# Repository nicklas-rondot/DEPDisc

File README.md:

# DEPDisc
The DEPDisc platform is the first implementation of dielectrophoresis where both the equipment and the consumables are truly inexpensive. It utilizes CD microfluidics to allow the integration of DEP with other microfluidic operations. 
All aspects of the DEPDisc platform are open-source, including the fabrication technique for the discs (with example designs) and the device.
While the paper presents the underlying theory and the results of the DEPDisc platform, this repository is intended to provide the necessary information to reproduce the platform.

This version is from the 06th of October 2024. A more current version might be available at https://github.com/nicklas-rn/DEPDisc.

## Table of Contents
- [Discs](#Discs)
- [Device](#Device)
- [How to Run](<#How to Run>)
- [Additional Figures](<#Additional Figures>)

## Discs
In the folder [Discs](/Discs), the design files for the discs can be found. The PCB files can be used in Eagle or Fusion360 Electronics. [Example Disc PCBs](/Discs/Example%20Disc%20PCBs) are provided as inspiration. The separate [coil PCB](/Discs/Coil%20PCB/) used as transmitter is included as well. For new designs, the [coil PCB library](/Discs/Coil%20PCB%20Library/) can be used.

## Device
The [Device CAD and PCB folder](/Device/) contains all the necessary files to reproduce the DEPDisc device. The device is composed of a PCB, off-the-shelf components, and a set of 3D printed parts. 

### PCB
To order the PCB at [JLCPCB](https://jlcpcb.com), the [Manufacturing folder](/Device/PCB/Manufacturing/) with a [ZIP file](/Device/PCB/Manufacturing/DEPDisc%20Base%20rev1%20v8_2024-09-17.zip) of the Gerber files is included. For assembly by JLCPCB, the [BOM file](/Device/PCB/Manufacturing/DEPDisc%20Base%20rev1%20v8_2024-09-17.zip) and [Pick and Place file](/Device/PCB/Manufacturing/DEPDisc%20Base%20rev1%20v8_2024-09-17.zip) are also provided. 
The ordering process is the follwing:
1. Go to [JLCPCB](https://jlcpcb.com)
2. Click on **Add gerber file** and upload the ZIP file
3. Select the desired options and **Enable PCB Assembly** (choose 2 as PCBA quantity instead of 5). Select **Bottom Side Assembly**.
4. After clicking **Next**, upload the **BOM file** and **CPL (Pick and Place) file**, then continue
5. When reviewing the parts, ensure that only C13 and JP3 show 'No part selected' and that the rest of the parts are correctly assigned. Then click **Next** and then **Do not Place** upon the prompt showing that the project has unselected parts.
6. Review the part placement and click **Next**, then click **Save to Cart**
7. Review the order and click **Secure Checkout**

The [design files](/Device/PCB/Design%20Files) of the PCB for Eagle or Fusion360 Electronics are included in case this project is used as inspiration or if modifications are desired.

### Housing
The [parts for printing](/Device/3D%20Printed%20Parts) are provided as STL files. In the slicer, we recommend enabling tree-supports. 
A [STEP file](/Device/DEPDisc%20Device%20rev1.step) of the assembly is included. 

### Assembly
To assemble the device, use the following procedure:
1. Place M3 nuts in all the provided slots in the 3D printed parts.
2. Solder the pin-headers to the PCB: 
3. Solder two jumper wires to the motor: 
4. Plug the ESP32 NodeMCU Dev board into the pin-headers: 
5. Screw the touch display to the display mount: 
6. Plug in 14 female-to-female jumper wires to the display. We recommend placing tape around the ends to keep the wires together when they are removed: 
7. Plug the other side of the jumper wires into the PCB: 
8. Slide the PCB into the left side of the inner shell of the housing and move the motor through the hole: 
9. Screw the motor in place with two M1.2 screws: 
10. Slide the display in to the right side of the inner shell of the housing: 
11. Screw the display in place from the bottom with four M3 screws: 
12. Connect the two inner shell sides with three M3 screws:  
13. Place the right side of the outer shell on top of the inner shell by carefully bending it slightly: 
14. Push the aluminium rod through the left side of the outer shell and the hatch: 
15. Push the left side of the outer shell on top of the inner shell by moving it in from the left and carefully bending it slightly:  
16. Screw six M3 screws into the outer shell: 

### Programming
To program the device, use the [Arduino file](/Device/Software/DEPDisc_base.ino) provided in the [Software folder](/Device/Software). Use to following procedure:
1. Download the Arduino IDE
2. Install the ESP32 boards under the boards manager (Second tab from the top, type 'esp32' in the search bar, and click install)
3. Click on Tools -> Board -> esp32 -> ESP32 Dev Module
4. Select the correct port under Tools -> Port
5. Click on the upload button (right arrow) to upload the code to the ESP32

## How to Run
### Experimental mode
Connect the device with a USB cable to a laptop. Use the Serial Monitor of the Arduino IDE and select a Baud Rate of 115200. 
To set a specific frequency, type: `freq [frequency in Hz]`
To set a specific speed, type: spin `[PWM value between -255 and 255]`

### Run from SD card
Write a text file with the name **run.txt** to the SD card with the same commands as above. Between the commands use a newline. Use the command `delay [delay in seconds]` to set delays. Insert the SD card into the device and select 'Run from SD card'. The device will read the file and execute the commands.

## Additional Figures
- [A video showing the attraction of yeast cells to the edges of two electrodes](/Figures/dep_edge.mov).

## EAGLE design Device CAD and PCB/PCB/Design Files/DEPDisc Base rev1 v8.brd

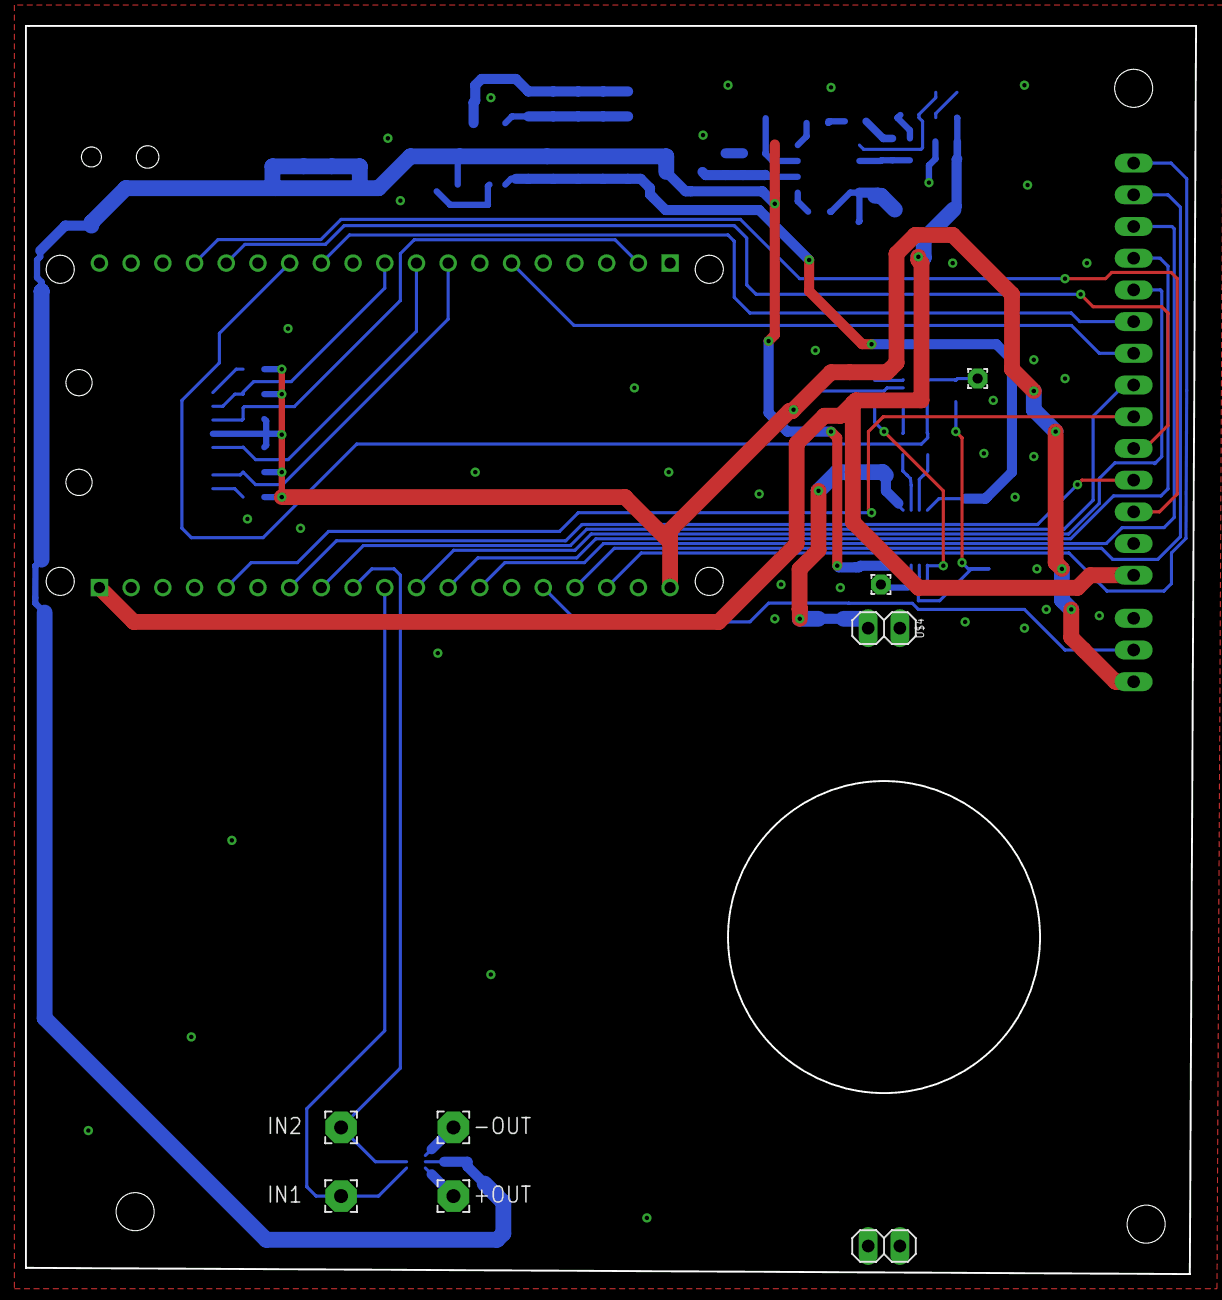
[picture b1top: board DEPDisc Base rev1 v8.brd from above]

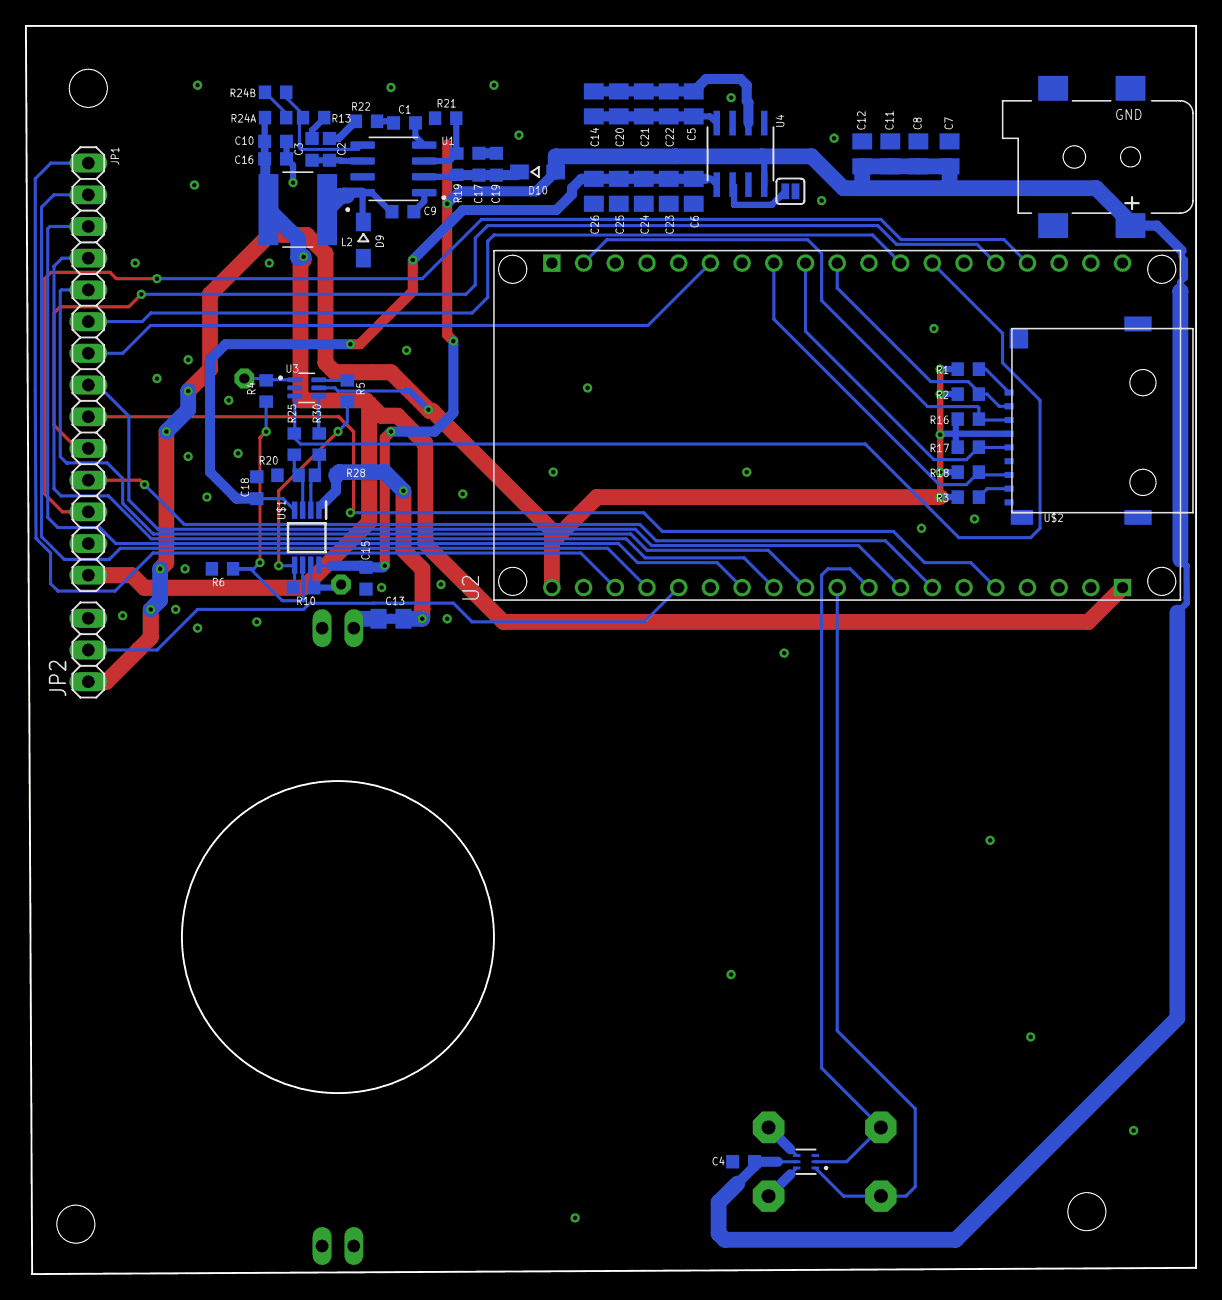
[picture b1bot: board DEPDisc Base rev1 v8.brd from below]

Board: 2 copper layers, 93.8 x 100.0 mm, 68 parts (60 on the bottom side), 50 nets.

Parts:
+OUT: 2,54/1,1
-OUT: 2,54/1,1
AMPIN2: 1,6/0,8
AMPOUT2: 1,6/0,8
C1, C17: 10nF; C0603K
C2: 1nF; C0603K
C3: 47pF; C0603K
C4, C9, C15, C18: 100nF; C0603K
C5, C6, C7, C8, C11, C12, C14, C20, C21, C22, C23, C24, C25, C26: 22uF; C0805K
C10, C16: 47uF; C0603K
C13: DNP; C0805K
C19: 10uF; C0603K
CN1: DC-005-2.5A-2.0-SMT; DCJACK_2MM_SMT
D9, D10: 1N5819WS; SOD323-W
IN1, IN2: 2,54/1,1
JP1: 1X14
JP2: 1X03
JP3: JUMPER-SMT_2_NC_PASTE_SILK; SMT-JUMPER_2_NC_PASTE_SILK
L2: 1255AY-6R8M=P3; IND_1255AY-6R8M=P3
R1, R2, R3, R16, R17, R18: 47k; R0603
R4, R5, R24B: 510; R0603
R6, R10: 1k; R0603
R13, R20, R28: 2k; R0603
R19: 332k; R0603
R21: 68.1k; R0603
R22: 29.4k; R0603
R24A: 10k; R0603
R25, R30: 750; R0603
U1: TPS54331DR; SOIC127P599X175-8N
U2: ESP32_NODEMCU; MODULE_ESP32_NODEMCU
U3: SN74LVC2G04DCKR; SOT65P210X110-6N
U4: ICL7662EBA-T; 21-0041B_8
U5: DRV8220DRLRSOT5X3-6_DRL_TEX-L; SOT5X3-6_DRL_TEX-L
U$1: OPA2810IDGKR; SOP65P490X110-8N
U$2: MICROSD-PUSH-OUT
U$3, U$4: PINHD-1X02_1X02M; 1X02

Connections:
+3V3: JP2.1, R1.1, R2.1, R3.1, R16.1, R17.1, R18.1, U2.J5_19, U3.5, U$2.4
+5V: C10.1, C16.1, JP1.14, L2.2, R24A.2, U2.J5_1
+12V: C4.1, C7.2, C8.2, C11.2, C12.2, C15.1, CN1.PWR1, D10.A, U4.8, U5.5, U$1.8
+IN1: R25.2, U2.J4_13, U3.3
+IN1R: R20.2, R25.1, U$1.3
+IN2: AMPIN2.1, R4.2, U3.1
+IN2R: R4.1, R6.2, U$1.6
-12V: C6.2, C18.1, C23.2, C24.2, C25.2, C26.2, U4.5, U$1.4
-IN1: R30.2, U3.4
-IN1R: R28.1, R30.1, U$1.2
-IN2: R5.2, U3.6
-IN2R: R5.1, R10.1, U$1.5
AMP1: C13.1, C13.2, R28.2, U$1.1, U$4.1
AMP2: AMPOUT2.1, R10.2, U$1.7
DAT2: R1.2, U$2.1
GND: C1.2, C3.2, C4.2, C6.1, C7.1, C8.1, C10.2, C11.1, C12.1, C15.2, C16.2, C17.2, C18.2, C19.2, C23.1, C24.1, C25.1, C26.1, CN1.GND, CN1.GNDBREAK, D9.A, JP1.13, JP2.3, JP3.2, R6.1, R13.1, R20.1, R21.1, R22.1, U1.7, U2.J4_1, U2.J4_7, U2.J5_6, U3.2, U4.3, U5.3, U$2.6, U$2.G1, U$2.G2, U$2.G3, U$2.G4, U$4.2
IO2: JP1.10, U2.J4_15
IO5: R2.2, U2.J4_10, U$2.2
IO12: JP1.11, U2.J5_7
IO13: JP1.9, U2.J5_5
IO14: JP1.8, U2.J5_8
IO15: JP1.12, U2.J4_16
IO16: JP1.6, U2.J4_12
IO18: R17.2, U2.J4_9, U$2.5
IO19: R18.2, U2.J4_8, U$2.7
IO21: JP1.7, U2.J4_6
IO23: R16.2, U2.J4_2, U$2.3
IO25: JP1.5, U2.J5_11
IO26: IN1.1, U2.J5_10, U5.1
IO27: IN2.1, U2.J5_9, U5.2
IO32: JP1.3, U2.J5_13
IO33: JP1.4, U2.J5_12
IO34: JP2.2, U2.J5_15
IO36: JP1.1, U2.J5_17
IO39: JP1.2, U2.J5_16
unnamed: C5.2, C14.2, C20.2, C21.2, C22.2, U4.2
unnamed: C5.1, C14.1, C20.1, C21.1, C22.1, U4.4
unnamed: +OUT.1, U5.6
unnamed: -OUT.1, U5.4
unnamed: JP3.1, U4.6
unnamed: R19.2, R21.2, U1.3
unnamed: C1.1, U1.4
unnamed: R3.2, U$2.8
unnamed: C2.1, C3.1, U1.6
unnamed: C2.2, R22.2
unnamed: R24A.1, R24B.2
unnamed: C9.2, U1.1
unnamed: C17.1, C19.1, D10.C, R19.1, U1.2
PH: C9.1, D9.C, L2.1, U1.8
VSENSE: R13.2, R24B.1, U1.5

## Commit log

2024-10-05 feat: started README
2024-10-05 feat: completed first version of README
2024-10-05 fix: left outer shell images
2024-10-05 feat: added video
2024-10-05 feat: embedded video in README
2024-10-05 fix: removed video as it could not play
2024-10-05 feat: added video to readme and changed software file
2024-10-06 feat: STLs added
2024-10-06 feat: added Word file and updated README

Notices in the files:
parts and their libraries:
SparkFun-Jumpers: Licensing: Creative Commons ShareAlike 4.0 International - https://creativecommons.org/licenses/by-sa/4.0
COPYRIGHT: Copyright (C) 2024 Ultra Librarian. All rights reserved.
